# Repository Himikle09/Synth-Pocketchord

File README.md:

# Synth-Pocketchord
Designing a pocketchord / synth / music player device.
Initially, I tested physically using an arduino, a breadboard, some button, and wires. The result was quite successful, but the practicality of such a system wasn't great. I decided to use this project to learn how to use KiCad and first designed a schematic and then a PCB. The purpose of the music player, is to have an array of larger buttons that controls notes. It would most likely have 7 notes with the button above being the note exactly an octave above the lower, and the lower button would be sort of a harmonizer button, to always be able to play a nice chord. The 12 smaller buttons on the right controll recording, looping, kick, snare, chord/notes and much more. The joystick controlls pitch and overall octave.

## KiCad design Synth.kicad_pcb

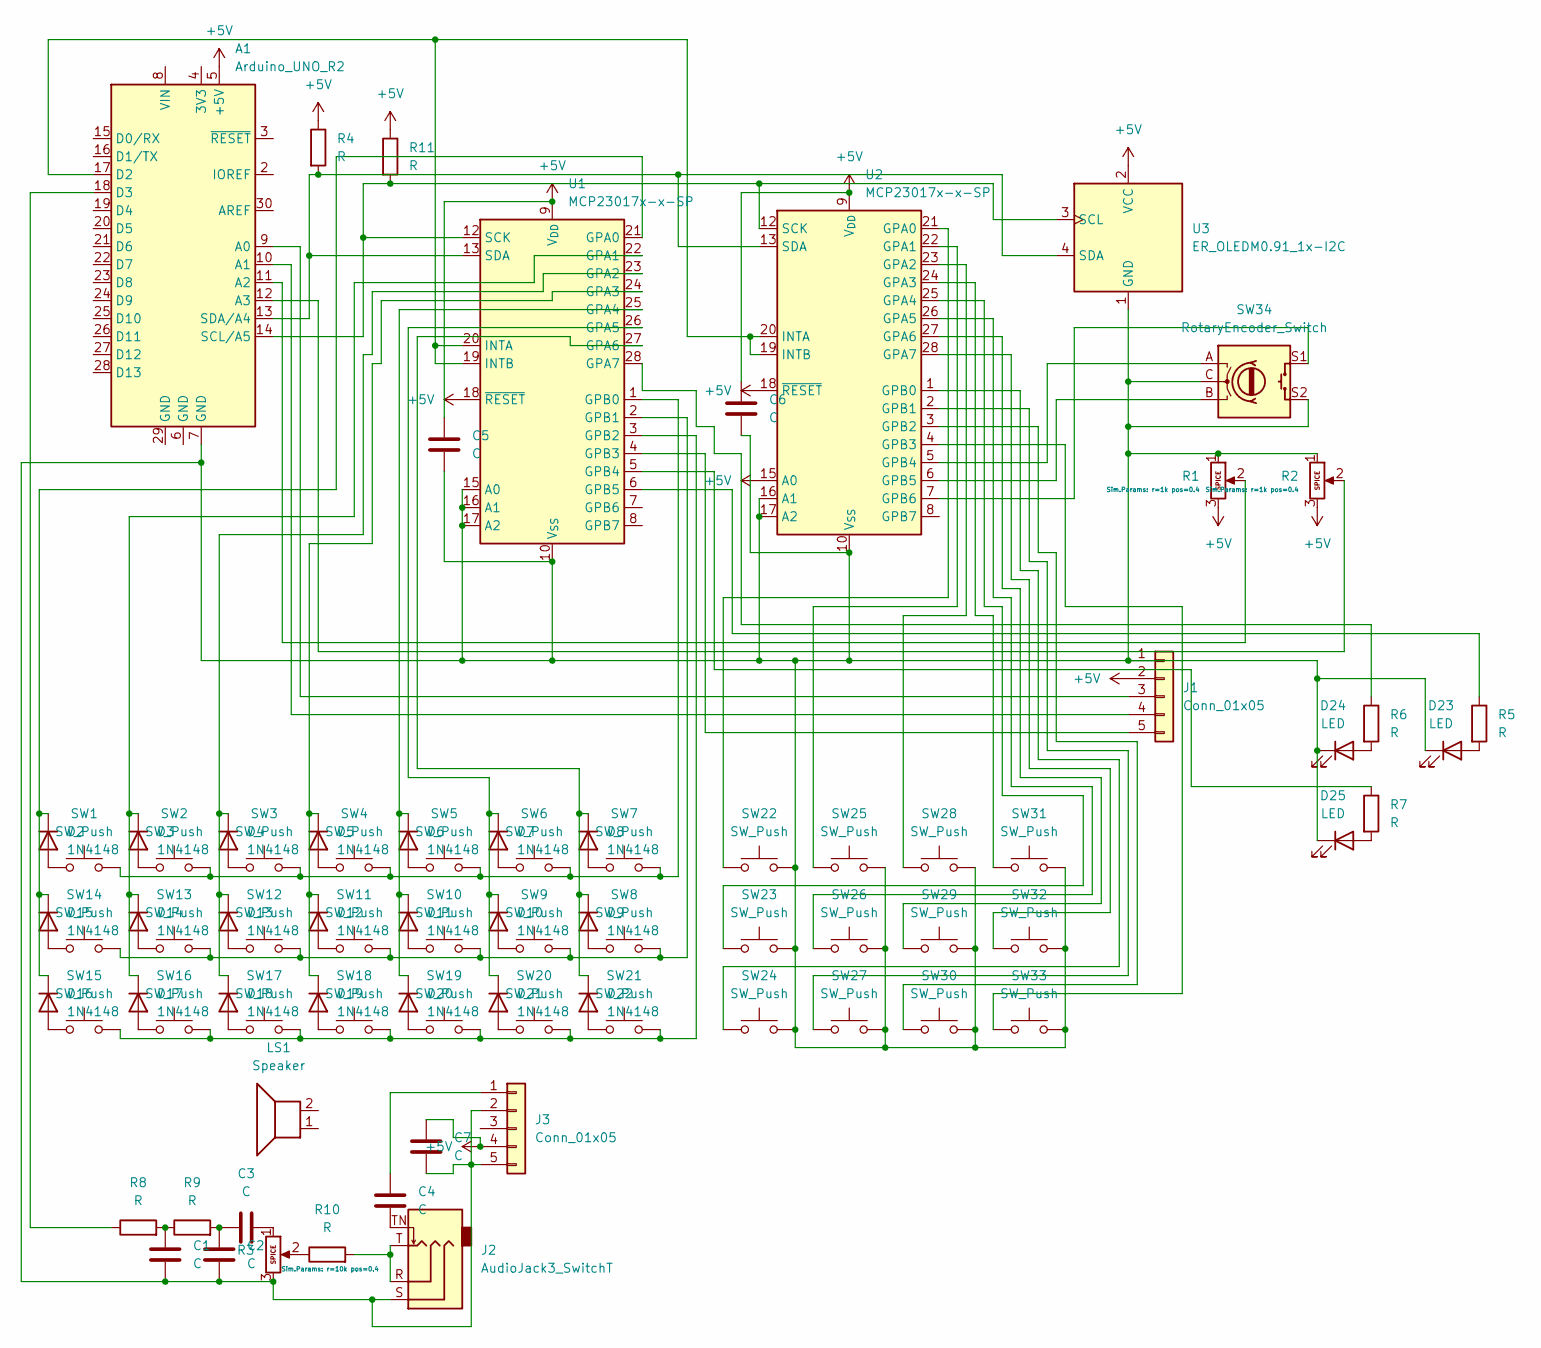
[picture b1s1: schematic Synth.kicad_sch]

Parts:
A1: Arduino_UNO_R2
C1, C2, C4, C5, C6: C; C_Disc_D5.0mm_W2.5mm_P5.00mm
C3: C; CP_Radial_D5.0mm_P2.00mm
C7: C; CP_Radial_D8.0mm_P3.50mm
D2, D3, D4, D5, D6, D7, D8, D9, D10, D11, D12, D13, D14, D15, D16, D17, D18, D19, D20, D21, D22: 1N4148; D_DO-35_SOD27_P7.62mm_Horizontal
D23, D24, D25: LED; LED_D3.0mm
J1, J3: Conn_01x05; PinHeader_1x05_P2.54mm_Vertical
J2: AudioJack3_SwitchT; Jack_3.5mm_CUI_SJ-3524-SMT_Horizontal
LS1: Speaker
R1, R2, R3: Potentiometer; Potentiometer_Alps_RK09K_Single_Vertical
R4, R5, R6, R7, R8, R9, R10, R11: R; R_Axial_DIN0207_L6.3mm_D2.5mm_P7.62mm_Horizontal
SW1, SW2, SW3, SW4, SW5, SW6, SW7, SW8, SW9, SW10, SW11, SW12, SW13, SW14, SW15, SW16, SW17, SW18, SW19, SW20, SW21: SW_Push; SW_PUSH-12mm
SW22, SW23, SW24, SW25, SW26, SW27, SW28, SW29, SW30, SW31, SW32, SW33: SW_Push; SW_PUSH_6mm
SW34: RotaryEncoder_Switch; RotaryEncoder_Alps_EC11E-Switch_Vertical_H20mm
U1, U2: MCP23017x-x-SP; DIP-28_W7.62mm
U3: ER_OLEDM0.91_1x-I2C

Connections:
+5V: A1.5 (+5V), C5.1, C6.1, C7.1, J1.2, J3.4, R1.3, R2.3, R4.1, R11.1, U1.9 (V_{DD}), U1.18 (~RESET), U2.9 (V_{DD}), U2.15 (A0), U2.18 (~RESET), U3.2 (VCC)
unnamed: A1.9 (A0), J1.3
unnamed: A1.10 (A1), J1.4
unnamed: A1.11 (A2), R1.2
unnamed: A1.12 (A3), R2.2
unnamed: A1.17 (D2), U1.19 (INTB), U1.20 (INTA), U2.19 (INTB), U2.20 (INTA)
unnamed: A1.18 (D3), R8.1
unnamed: A1.14 (SCL/A5), R11.2, U1.12 (SCK), U2.12 (SCK), U3.3 (SCL)
unnamed: A1.13 (SDA/A4), R4.2, U1.13 (SDA), U2.13 (SDA), U3.4 (SDA)
unnamed: C1.1, R8.2, R9.1
unnamed: C2.1, C3.1, R9.2
unnamed: C3.2, R3.1
unnamed: C4.1, J3.1
unnamed: C4.2, J2.TN
unnamed: D2.2 (A), SW1.1
unnamed: D3.2 (A), SW2.1
unnamed: D4.2 (A), SW3.1
unnamed: D5.2 (A), SW4.1
unnamed: D6.2 (A), SW5.1
unnamed: D7.2 (A), SW6.1
unnamed: D8.2 (A), SW7.1
unnamed: D9.2 (A), SW8.1
unnamed: D10.2 (A), SW9.1
unnamed: D7.1 (K), D10.1 (K), D21.1 (K), U1.26 (GPA5)
unnamed: D11.2 (A), SW10.1
unnamed: D6.1 (K), D11.1 (K), D20.1 (K), U1.25 (GPA4)
unnamed: D12.2 (A), SW11.1
unnamed: D5.1 (K), D12.1 (K), D19.1 (K), U1.24 (GPA3)
unnamed: D13.2 (A), SW12.1
unnamed: D4.1 (K), D13.1 (K), D18.1 (K), U1.23 (GPA2)
unnamed: D14.2 (A), SW13.1
unnamed: D3.1 (K), D14.1 (K), D17.1 (K), U1.22 (GPA1)
unnamed: D15.2 (A), SW14.1
unnamed: D2.1 (K), D15.1 (K), D16.1 (K), U1.21 (GPA0)
unnamed: D16.2 (A), SW15.1
unnamed: D17.2 (A), SW16.1
unnamed: D18.2 (A), SW17.1
unnamed: D19.2 (A), SW18.1
unnamed: D20.2 (A), SW19.1
unnamed: D21.2 (A), SW20.1
unnamed: D22.2 (A), SW21.1
unnamed: D8.1 (K), D9.1 (K), D22.1 (K), U1.27 (GPA6)
unnamed: D23.2 (A), R5.2
unnamed: A1.7 (GND), C1.2, C2.2, C5.2, C6.2, C7.2, D23.1 (K), D24.1 (K), D25.1 (K), J1.1, J2.S, J3.2, J3.5, R1.1, R2.1, R3.3, SW22.2, SW23.2, SW24.2, SW25.2, SW26.2, SW27.2, SW28.2, SW29.2, SW30.2, SW31.2, SW32.2, SW33.2, SW34.C, SW34.S2, U1.10 (V_{SS}), U1.15 (A0), U1.16 (A1), U1.17 (A2), U2.10 (V_{SS}), U2.16 (A1), U2.17 (A2), U3.1 (GND)
unnamed: D24.2 (A), R6.2
unnamed: D25.2 (A), R7.2
unnamed: J1.5, U1.4 (GPB3)
unnamed: J2.R, J2.T, R10.2
unnamed: R3.2, R10.1
unnamed: R6.1, U1.28 (GPA7)
unnamed: SW1.2, SW2.2, SW3.2, SW4.2, SW5.2, SW6.2, SW7.2, U1.1 (GPB0)
unnamed: SW8.2, SW9.2, SW10.2, SW11.2, SW12.2, SW13.2, SW14.2, U1.2 (GPB1)
unnamed: SW15.2, SW16.2, SW17.2, SW18.2, SW19.2, SW20.2, SW21.2, U1.3 (GPB2)
unnamed: R7.1, U1.5 (GPB4)
unnamed: R5.1, U1.6 (GPB5)
unnamed: SW22.1, U2.21 (GPA0)
unnamed: SW25.1, U2.22 (GPA1)
unnamed: SW28.1, U2.23 (GPA2)
unnamed: SW31.1, U2.24 (GPA3)
unnamed: SW23.1, U2.25 (GPA4)
unnamed: SW26.1, U2.26 (GPA5)
unnamed: SW29.1, U2.27 (GPA6)
unnamed: SW32.1, U2.28 (GPA7)
unnamed: SW24.1, U2.1 (GPB0)
unnamed: SW27.1, U2.2 (GPB1)
unnamed: SW30.1, U2.3 (GPB2)
unnamed: SW33.1, U2.4 (GPB3)
unnamed: SW34.A, U2.5 (GPB4)
unnamed: SW34.B, U2.6 (GPB5)
unnamed: SW34.S1, U2.7 (GPB6)

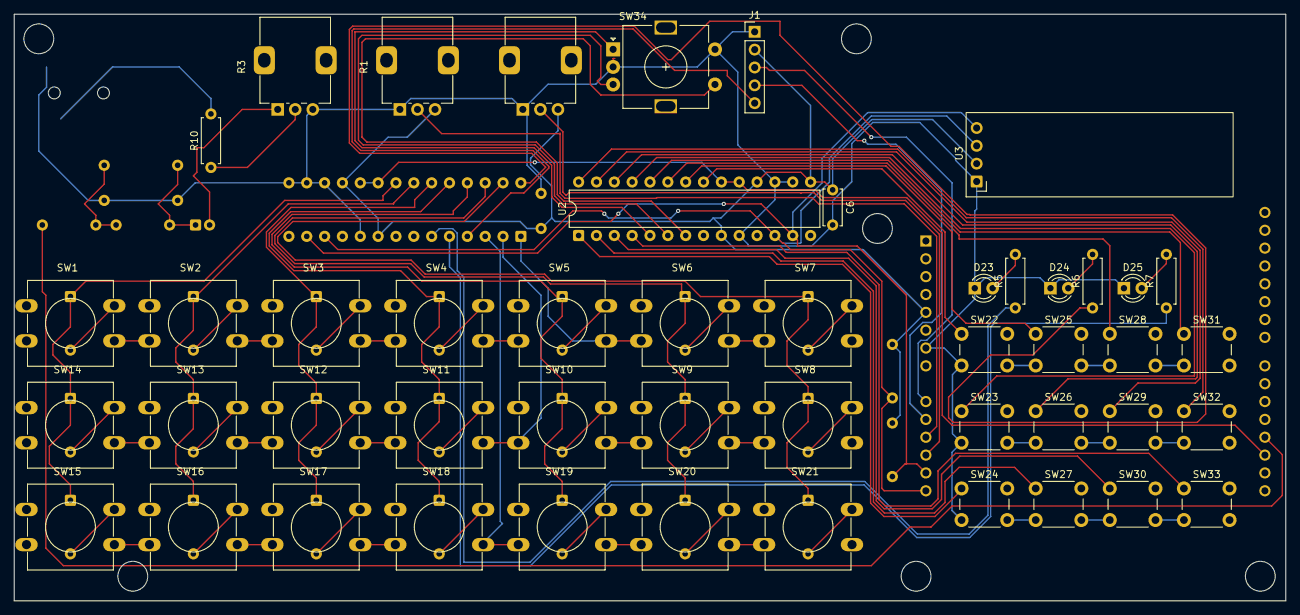
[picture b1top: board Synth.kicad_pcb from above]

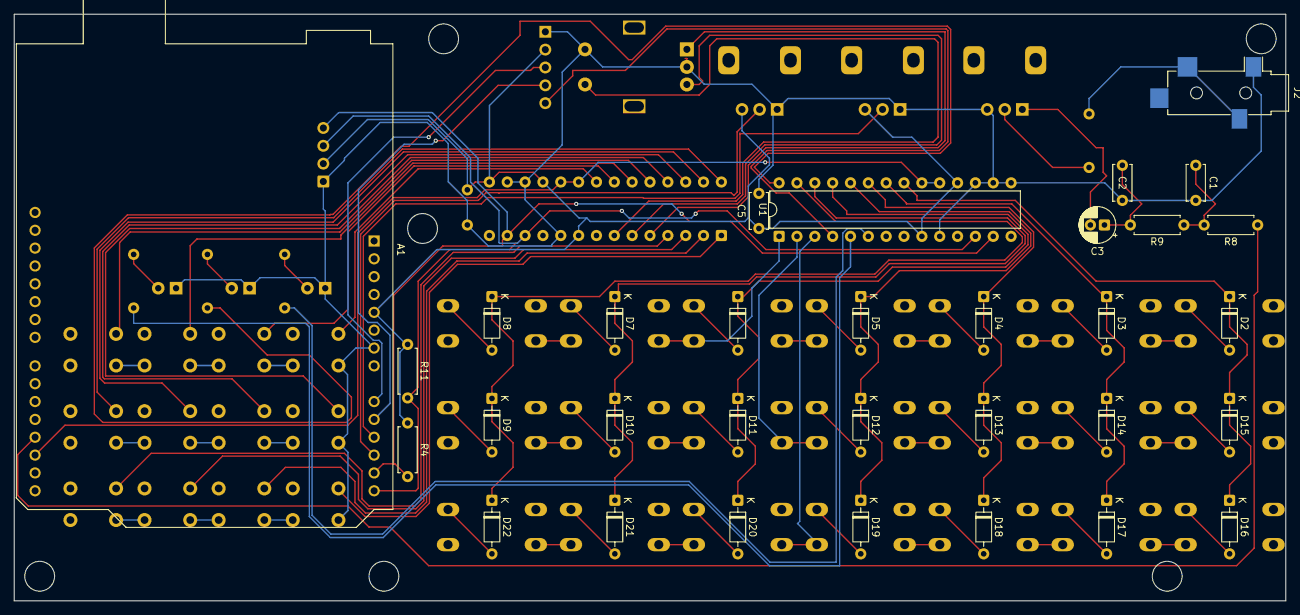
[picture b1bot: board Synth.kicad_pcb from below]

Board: 2 copper layers, 181.0 x 83.5 mm, 80 parts (32 on the bottom side), 68 nets.
